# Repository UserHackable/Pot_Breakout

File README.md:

## For Arduino 

I created this board to act as a mini shield to provide an easy way to have four analog adjustments on the Arduino with A0 through A3

It uses a common and inexpensive trim-pot form factor, but makes it much easier to connect them to the arduino. 

## PotBreakout 

### Board dimensions

* (130000, 50000) original units
* (1.3000, 0.5000) inches
* (33.0200, 12.7000) mm

| Front | Back |
| --- | --- |
|  |  |

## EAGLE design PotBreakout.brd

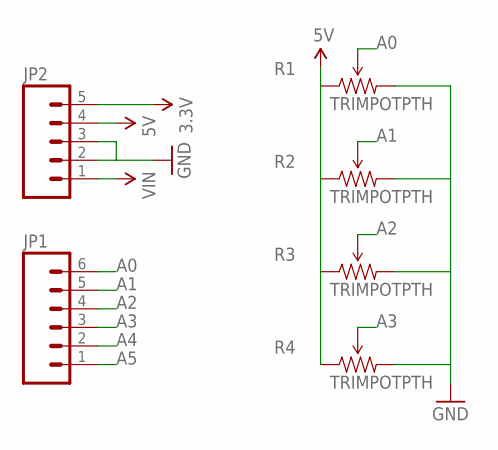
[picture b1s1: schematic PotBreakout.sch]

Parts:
JP1: M06SIP; 1X06
JP2: M05NO_SILK; 1X05_NO_SILK
R1, R2, R3, R4: TRIMPOTPTH; TRIM_POT_PTH

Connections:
3.3V: JP2.5
5V: JP2.4, R1.1 (CCW), R2.1 (CCW), R3.1 (CCW), R4.1 (CCW)
A0: JP1.6, R1.2 (WIPER)
A1: JP1.5, R2.2 (WIPER)
A2: JP1.4, R3.2 (WIPER)
A3: JP1.3, R4.2 (WIPER)
A4: JP1.2
A5: JP1.1
GND: JP2.2, JP2.3, R1.3 (CW), R2.3 (CW), R3.3 (CW), R4.3 (CW)
VIN: JP2.1

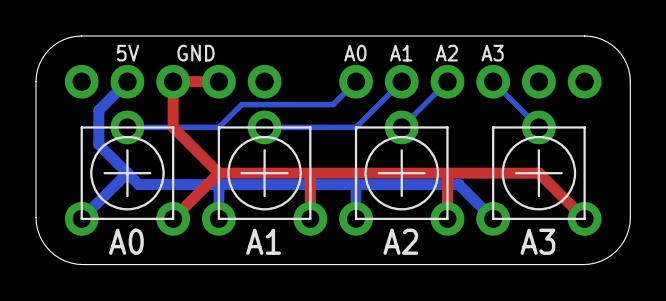
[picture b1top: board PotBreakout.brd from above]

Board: 2 copper layers, 33.0 x 12.7 mm, 6 parts (0 on the bottom side), 6 nets.

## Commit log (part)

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2016-04-08 from Makefile

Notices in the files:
parts and their libraries:
SparkFun-Connectors: Licensing: Creative Commons ShareAlike 4.0 International - https://creativecommons.org/licenses/by-sa/4.0
